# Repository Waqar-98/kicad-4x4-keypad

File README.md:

# Keypad 4x4

A 4x4 matrix keypad PCB using 16 tactile push-button switches wired in a row/column matrix, broken out to a single 8-pin header for scanning by an external microcontroller.

| | |
|---|---|
| **Switches** | 16x KSC1131J (SMD tactile switch) |
| **Layers** | 2 |
| **Interfaces** | 8-pin matrix header (4 columns, 4 rows) |
| **Revision** | 0.1 |
| **Status** | In development |

---

## Table of Contents

1. [Overview](#1-overview)
2. [Features](#2-features)
3. [Hardware Description](#3-hardware-description)
4. [Schematic](#4-schematic)
5. [PCB Layout](#5-pcb-layout)
6. [Connector Pinout](#6-connector-pinout)
7. [Getting Started](#7-getting-started)
8. [Repository Structure](#8-repository-structure)
9. [Bill of Materials](#9-bill-of-materials)
10. [Revision History](#10-revision-history)
11. [License](#11-license)

---

## 1. Overview

This board implements a 4x4 tactile matrix keypad intended for use as an input peripheral for a microcontroller-based project. Sixteen SMD tactile switches (S1-S16) are arranged in a 4-row by 4-column grid and wired so the full keypad can be scanned using only 8 GPIO lines (4 column drives, 4 row reads) via a single in-line header. Four mounting holes are provided at the board corners for enclosure integration.

## 2. Features

- 16x KSC1131J SMD tactile switches arranged in a 4x4 matrix
- Single 8-pin header (J1) exposing 4 column lines and 4 row lines for matrix scanning
- Compact square form factor with four corner mounting holes (H1-H4)
- 2-layer PCB, fully routed on front and back copper
- No onboard active components — passive switch matrix only, driven and debounced externally by the host microcontroller

## 3. Hardware Description

The board consists of a single functional block: the switch matrix itself. Sixteen KSC1131J tactile switches are arranged in four rows of four. Each switch bridges a column net to a row net when pressed. Columns 1-4 and rows 5-8 are brought out to header J1, labeled pins 1 through 8 on the silkscreen, so the entire matrix can be scanned by a host microcontroller using a standard row/column GPIO scanning routine with no additional external components required on this board.

Four non-plated mounting holes (H1-H4) are placed at the corners of the board for mechanical mounting into an enclosure.

## 4. Schematic

## 5. PCB Layout

The board is a 2-layer design. Routing uses both front and back copper layers to connect the 16 switch footprints back to the 8-pin header without vias on the switch pads themselves, keeping the top layer clear under each keycap. Four plated mounting holes are located at the board corners.

**3D Render**

## 6. Connector Pinout

Pin assignments below are derived from the schematic and PCB silkscreen. Verify against the source design files prior to integration.

**J1 — Keypad Matrix Header (8-pin)**

| Pin | Signal |
|-----|--------|
| 1 | Column 1 |
| 2 | Column 2 |
| 3 | Column 3 |
| 4 | Column 4 |
| 5 | Row 1 |
| 6 | Row 2 |
| 7 | Row 3 |
| 8 | Row 4 |

## 7. Getting Started

1. **Connect:** Wire J1 to 8 GPIO pins on the host microcontroller — 4 outputs for the column lines (pins 1-4) and 4 inputs for the row lines (pins 5-8), or vice versa depending on the scanning scheme used.
2. **Pull configuration:** Configure the row (input) lines with pull-up or pull-down resistors on the host controller, since this board has no onboard biasing components.
3. **Scanning:** Drive one column low (or high) at a time and read the row lines to determine which key, if any, is pressed in that column. Repeat across all four columns to scan the full 4x4 matrix. Software debouncing is recommended, as no hardware debounce circuitry is present on this board.

## 8. Repository Structure

```
.
├── docs/
│   └── images/
│       ├── schematic.png
│       ├── pcb-layout.png
│       └── pcb-3d-render.png
├── hardware/
│   ├── kicad/            # KiCad project (.kicad_pro/.kicad_sch/.kicad_pcb kept
│   │                     # together so the project opens correctly)
│   ├── gerbers/          # Fabrication-ready Gerber and drill files
│   ├── step/             # 3D board model (.step)
│   ├── library/          # Vendor symbol/footprint/3D files for KSC1131J switch
│   └── bom.csv           # Bill of materials for assembly
├── archive/              # Old backups and export snapshots (not part of the design)
├── README.md
└── LICENSE
```

## 9. Bill of Materials

| Reference | Component | Description |
|---|---|---|
| S1-S16 | KSC1131J | SMD tactile push-button switch |
| J1 | Conn_01x08 | 8-pin single-row male header, matrix connection |
| H1-H4 | Mounting Hole | Corner mounting holes |

A machine-readable copy is available at [`hardware/bom.csv`](hardware/bom.csv). Manufacturer part numbers and LCSC/Digi-Key codes should be added once sourcing is finalized.

## 10. Revision History

| Revision | Date | Notes |
|---|---|---|
| 0.1 | 2026-07-29 | Initial release |

## 11. License

This project is released under the [MIT License](LICENSE).

---

**Author:** Waqar

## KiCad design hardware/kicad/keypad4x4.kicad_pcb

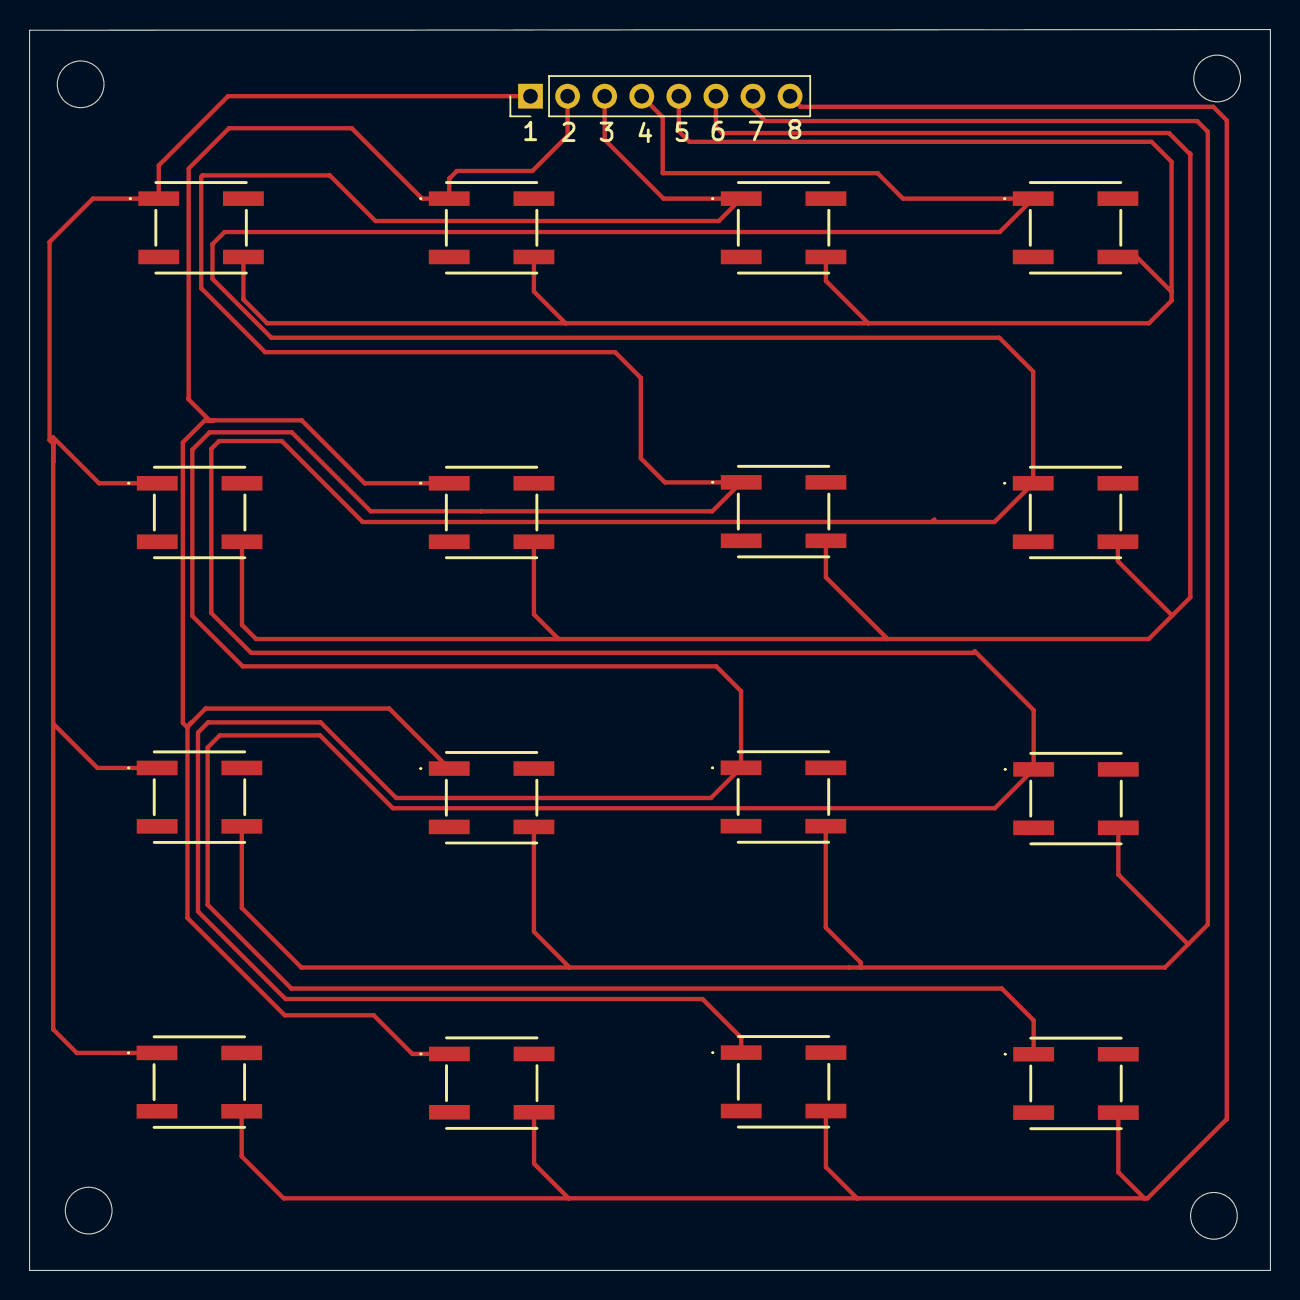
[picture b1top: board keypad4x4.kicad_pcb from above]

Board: 2 copper layers, 85.0 x 85.0 mm, 21 parts (0 on the bottom side), 8 nets.

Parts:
H1, H2, H3, H4: MountingHole; MountingHole_3.2mm_M3
J1: Conn_01x08; PinHeader_1x08_P2.54mm_Vertical
S1, S2, S3, S4, S5, S6, S7, S8, S9, S10, S11, S12, S13, S14, S15, S16: KSC1131J; KSC1131JLFS

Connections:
unnamed: J1.1, S1.1 (NO_1), S2.1 (NO_1), S3.1 (NO_1), S4.1 (NO_1)
unnamed: J1.2, S5.1 (NO_1), S6.1 (NO_1), S7.1 (NO_1), S8.1 (NO_1)
unnamed: J1.3, S9.1 (NO_1), S10.1 (NO_1), S11.1 (NO_1), S12.1 (NO_1)
unnamed: J1.4, S13.1 (NO_1), S14.1 (NO_1), S15.1 (NO_1), S16.1 (NO_1)
unnamed: J1.5, S1.4 (COM_2), S5.4 (COM_2), S9.4 (COM_2), S13.4 (COM_2)
unnamed: J1.6, S2.4 (COM_2), S6.4 (COM_2), S10.4 (COM_2), S14.4 (COM_2)
unnamed: J1.7, S3.4 (COM_2), S7.4 (COM_2), S11.4 (COM_2), S15.4 (COM_2)
unnamed: J1.8, S4.4 (COM_2), S8.4 (COM_2), S12.4 (COM_2), S16.4 (COM_2)

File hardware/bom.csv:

Reference,Quantity,Component,Description,Footprint
S1-S16,16,KSC1131J,SMD tactile push-button switch,KSC1131JLFS
J1,1,Conn_01x08,8-pin single-row male header (matrix connection),Conn_01x08_Pitch2.54mm
H1-H4,4,Mounting Hole,Corner mounting holes,MountingHole
